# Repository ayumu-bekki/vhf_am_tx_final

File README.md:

# VHF AM 送信用ファイナル段

VHF帯(144MHz)AM送信用ファイナル段の試験基板です。

## 仕様

| 項目 | 値 |
|------|-----|
| 電源電圧 | 5V〜7.2V |
| 対応MOSFET | 2SK3074 / HTL7G06S006P |

### 出力電力・入力レベル

| 電源 | MOSFET | 出力電力 | 入力レベル |
|------|--------|----------|------------|
| 5V | 2SK3074 | 125mW | 10mW (+10dBm / 2.0Vpp) |
| 7.2V | 2SK3074 | 500mW | 50mW (+17dBm / 4.5Vpp) |
| 5V | HTL7G06S006P | 750mW | 10mW (+10dBm / 2.0Vpp) |
| 7.2V | HTL7G06S006P | 1500mW | 20mW (+13dBm / 2.8Vpp) |

---

## インダクタの製作

### L2(フェライトコアチョークコイル)

- コア : 43材フェライトコア(例：FT-37-43)
- 線材 : 0.65mm ポリウレタン銅線
- 巻き数
  - 3.3μH : 3回巻き

### L1, L3, L4, L5(空芯コイル)

- 線材 : 0.8mm ポリウレタン銅線
- コア : 空芯(外径5mmの軸を型に使用)
- 巻き数
  - 50nH : 3回巻き
  - 80nH : 4回巻き

---

## MOSFETごとの実装変更

### 2SK3074 の場合

- 回路図通りに実装する

### HTL7G06S006P の場合

- 以下のパーツを変更する

| 部位 | 部品 | 変更内容 |
|------|------|----------|
| 入力マッチング | C3 | 50pF トリマ |
| 出力マッチング | L3 | 40nH(2〜3回巻き) |
| 出力マッチング | C8 | 47pF を実装する |

---

## 調整方法

### 必要な機器

- 電流計
- NanoVNA
- TinySA

---

### 1. バイアス調整(アイドリング電流の設定)

FETがAB級リニアアンプとして動作するよう、無信号時のアイドリング電流を設定します。

**準備**

1. RF信号は入力しない
2. RV1を絞る(ゲート電圧が最低になる方向)
3. 電源ラインに電流計を直列に接続

**手順**

1. 電源を入れる(この時点では数mA程度しか流れない)
2. RV1をゆっくり回していくと、電流が流れ始める点がある
3. 電流が **20〜30mA** になる位置でRV1を止める

---

### 2. 入力マッチング調整

NanoVNAを使って、アンプ入力のインピーダンスを50Ωに合わせます。
電源は入れた状態で測定する必要があります。

1. NanoVNAを144MHz中心にスキャン設定し、S11(反射係数 / SWR)を表示
2. NanoVNA CH0をアンプの入力コネクタ(J1)に接続
3. スミスチャートまたはSWRグラフを見ながら、トリマコンデンサ **C1** を回して **144MHzでSWR最小** となる点に合わせる

---

### 3. 出力マッチング調整

実際に電源・RF信号を入力して出力パワーを最大化します。

1. 入力(J1)に144MHzの信号源を接続
2. 出力(J3)に30dBアッテネータ → TinySA を接続
3. TinySAで144MHz付近のスペクトラムを表示
4. アンテナ側トリマ **C6** を回してピークが最大になる点を探す
5. FET側トリマ **C4** を回してさらにピークが高くなる点を探す
6. C6とC4を交互に調整し、ピーク点を追い込む

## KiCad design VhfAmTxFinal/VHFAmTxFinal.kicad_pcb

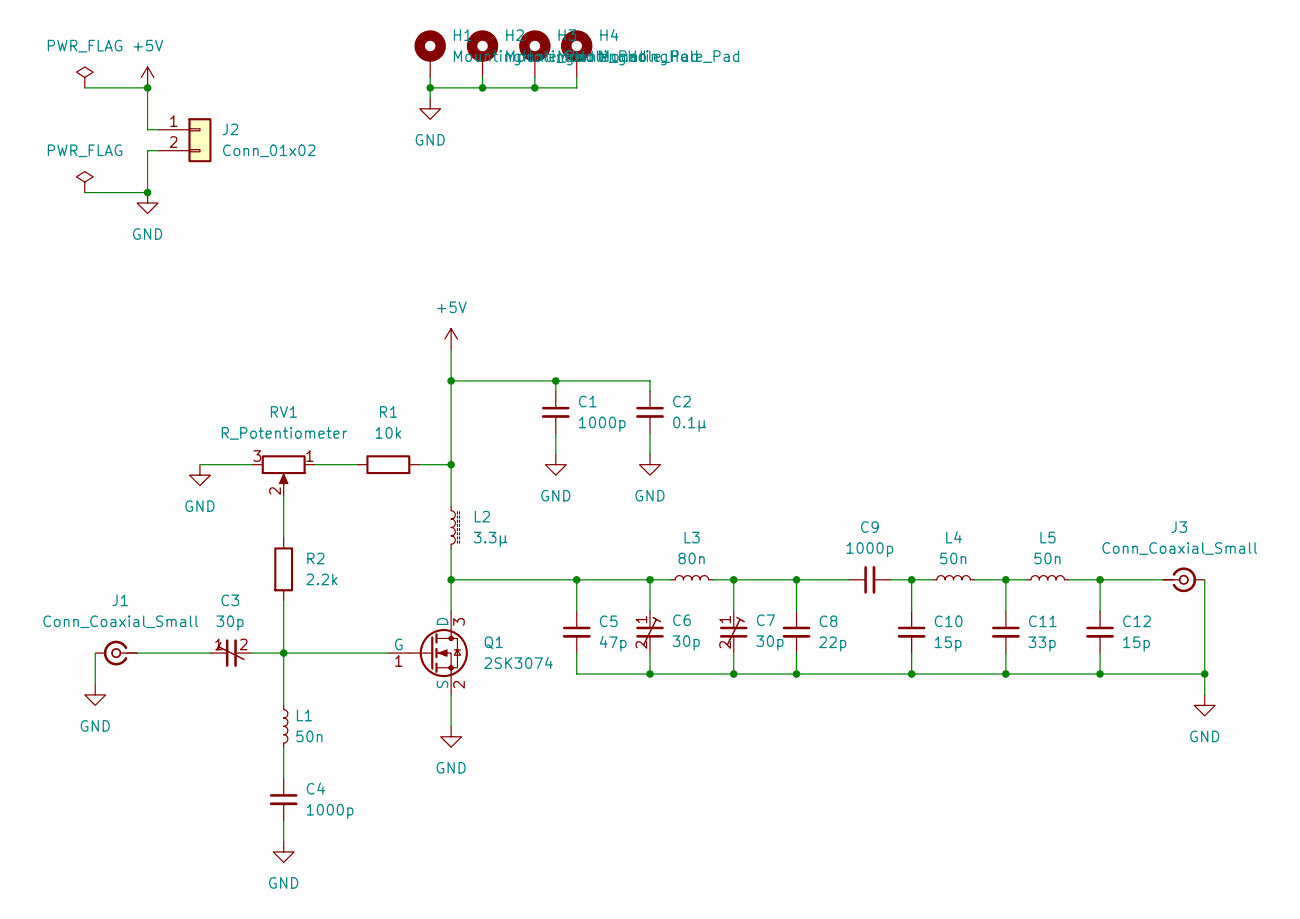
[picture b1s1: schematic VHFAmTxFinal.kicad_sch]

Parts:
C1, C4, C9: 1000p; C_0603_1608Metric_Pad1.08x0.95mm_HandSolder
C2: 0.1μ; C_0603_1608Metric_Pad1.08x0.95mm_HandSolder
C3, C6, C7: 30p; Ceramic_Trimmer_Capacitors_THT
C5: 47p; C_0603_1608Metric_Pad1.08x0.95mm_HandSolder
C8: 22p; C_0603_1608Metric_Pad1.08x0.95mm_HandSolder
C10, C12: 15p; C_0603_1608Metric_Pad1.08x0.95mm_HandSolder
C11: 33p; C_0603_1608Metric_Pad1.08x0.95mm_HandSolder
H1, H2, H3, H4: MountingHole_Pad; MountingHole_3.2mm_M3_Pad_Via
J1, J3: Conn_Coaxial_Small; SMA_S-063-49-TGG_EdgeMount_Horizontal
J2: Conn_01x02; JST_XH_S2B-XH-A_1x02_P2.50mm_Horizontal
L1, L4, L5: 50n; Air_Core_Inductor_8mm
L2: 3.3μ; Choke_Inductor_10mm
L3: 80n; Air_Core_Inductor_8mm
Q1: 2SK3074; SOT-89-3_Handsoldering
R1: 10k; R_0603_1608Metric_Pad0.98x0.95mm_HandSolder
R2: 2.2k; R_0603_1608Metric_Pad0.98x0.95mm_HandSolder
RV1: R_Potentiometer; Potentiometer_Vishay_T73YP_Vertical

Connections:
+5V: C1.1, C2.1, J2.1, L2.1, R1.2
GND: C1.2, C2.2, C4.2, C5.2, C6.2, C7.2, C8.2, C10.2, C11.2, C12.2, H1.1, H2.1, H3.1, H4.1, J1.2 (Ext), J2.2, J3.2 (Ext), Q1.2 (S), RV1.3
unnamed: C4.1, L1.2
unnamed: C7.1, C8.1, C9.1, L3.2
unnamed: C9.2, C10.1, L4.1
unnamed: C11.1, L4.2, L5.1
unnamed: C3.1, J1.1 (In)
unnamed: C12.1, J3.1 (In), L5.2
unnamed: C5.1, C6.1, L2.2, L3.1, Q1.3 (D)
unnamed: C3.2, L1.1, Q1.1 (G), R2.2
unnamed: R1.1, RV1.1
unnamed: R2.1, RV1.2

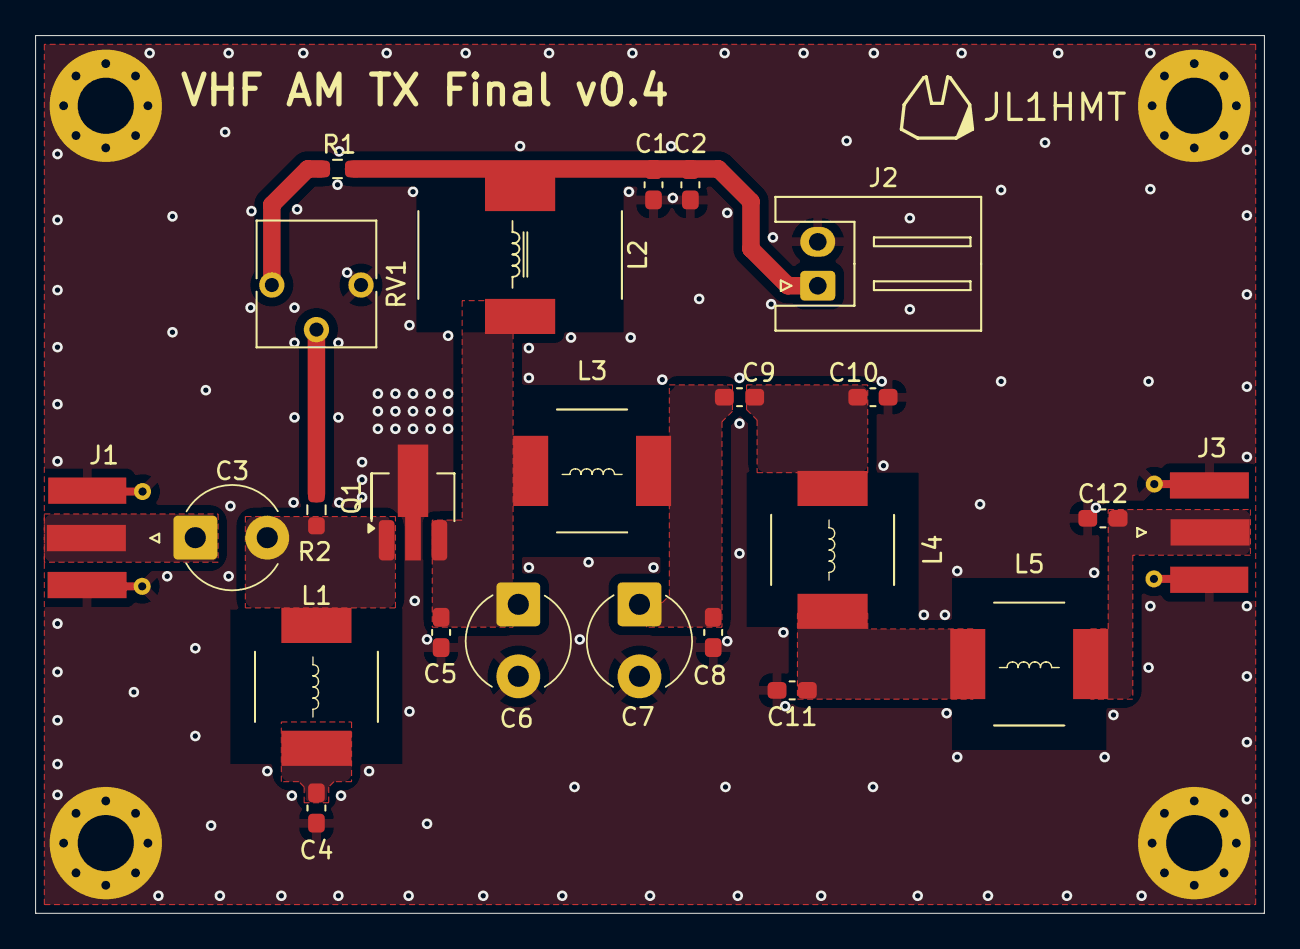
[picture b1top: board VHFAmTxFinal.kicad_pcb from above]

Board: 2 copper layers, 70.0 x 50.0 mm, 28 parts (0 on the bottom side), 12 nets.

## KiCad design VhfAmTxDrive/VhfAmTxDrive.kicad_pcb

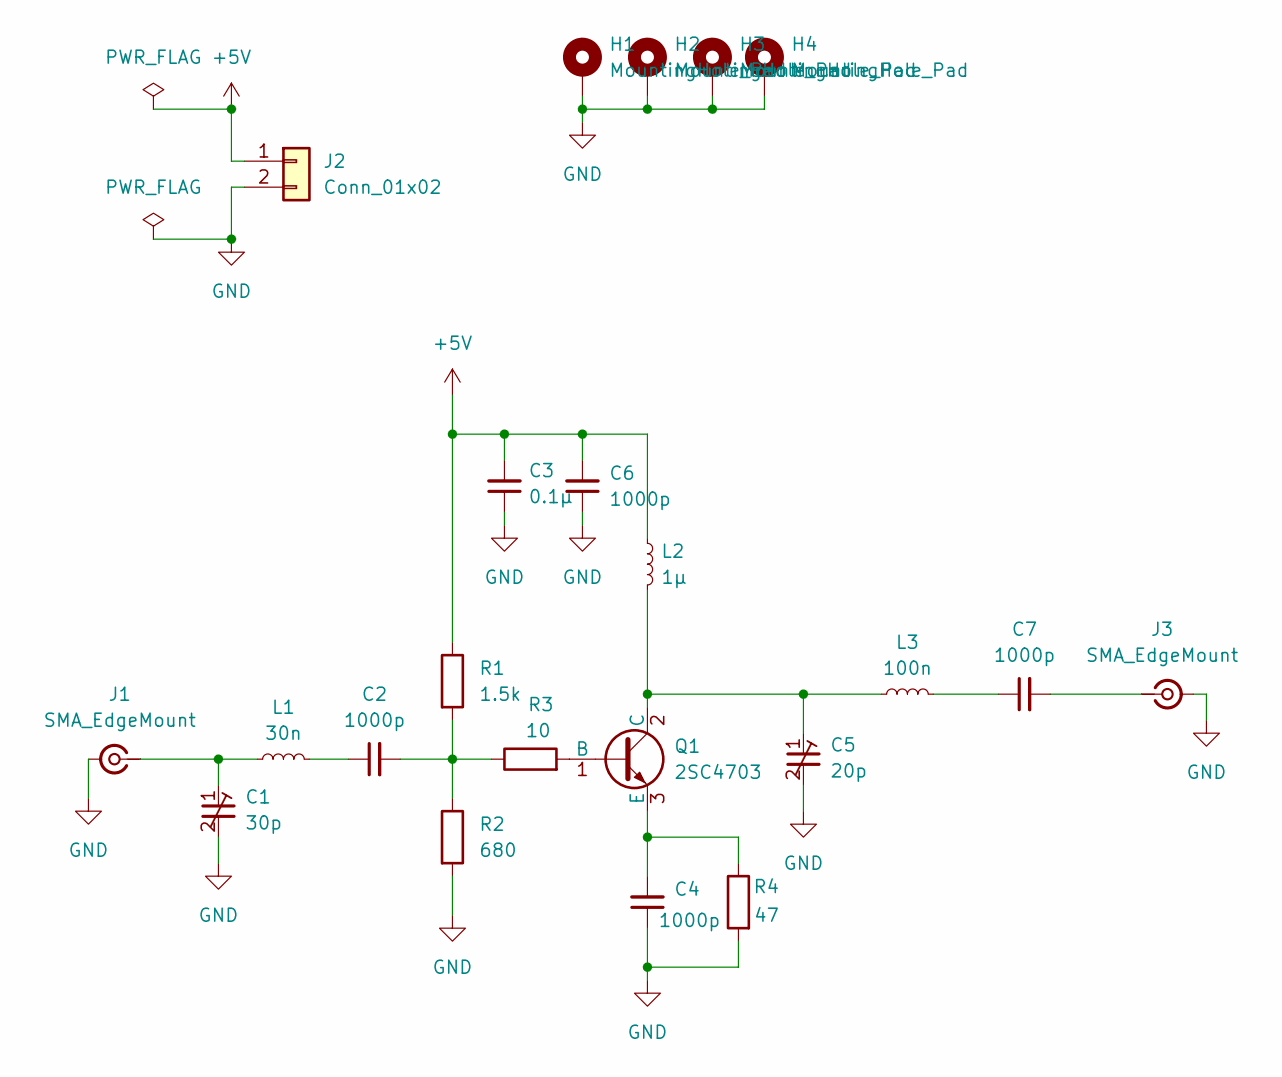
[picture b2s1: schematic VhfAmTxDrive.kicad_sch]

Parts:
C1: 30p; Ceramic_Trimmer_Capacitors_THT
C2, C4, C6, C7: 1000p; C_0603_1608Metric_Pad1.08x0.95mm_HandSolder
C3: 0.1μ; C_0603_1608Metric_Pad1.08x0.95mm_HandSolder
C5: 20p; Ceramic_Trimmer_Capacitors_THT
H1, H2, H3, H4: MountingHole_Pad; MountingHole_3.2mm_M3_Pad_Via
J1, J3: SMA_EdgeMount; SMA_S-063-49-TGG_EdgeMount_Horizontal
J2: Conn_01x02; JST_XH_S2B-XH-A_1x02_P2.50mm_Horizontal
L1: 30n; Air_Core_Inductor_8mm
L2: 1μ; Air_Core_Inductor_8mm
L3: 100n; Air_Core_Inductor_12mm
Q1: 2SC4703
R1: 1.5k; R_0603_1608Metric_Pad0.98x0.95mm_HandSolder
R2: 680; R_0603_1608Metric_Pad0.98x0.95mm_HandSolder
R3: 10; R_0603_1608Metric_Pad0.98x0.95mm_HandSolder
R4: 47; R_0603_1608Metric_Pad0.98x0.95mm_HandSolder

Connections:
+5V: C3.2, C6.2, J2.1, L2.1, R1.1
GND: C1.2, C3.1, C4.1, C5.2, C6.1, H1.1, H2.1, H3.1, H4.1, J1.2 (Ext), J2.2, J3.2 (Ext), R2.2, R4.2
unnamed: C2.1, L1.2
unnamed: C2.2, R1.2, R2.1, R3.1
unnamed: C7.1, L3.2
unnamed: C1.1, J1.1 (In), L1.1
unnamed: C7.2, J3.1 (In)
unnamed: Q1.1 (B), R3.2
unnamed: C5.1, L2.2, L3.1, Q1.2 (C)
unnamed: C4.2, Q1.3 (E), R4.1

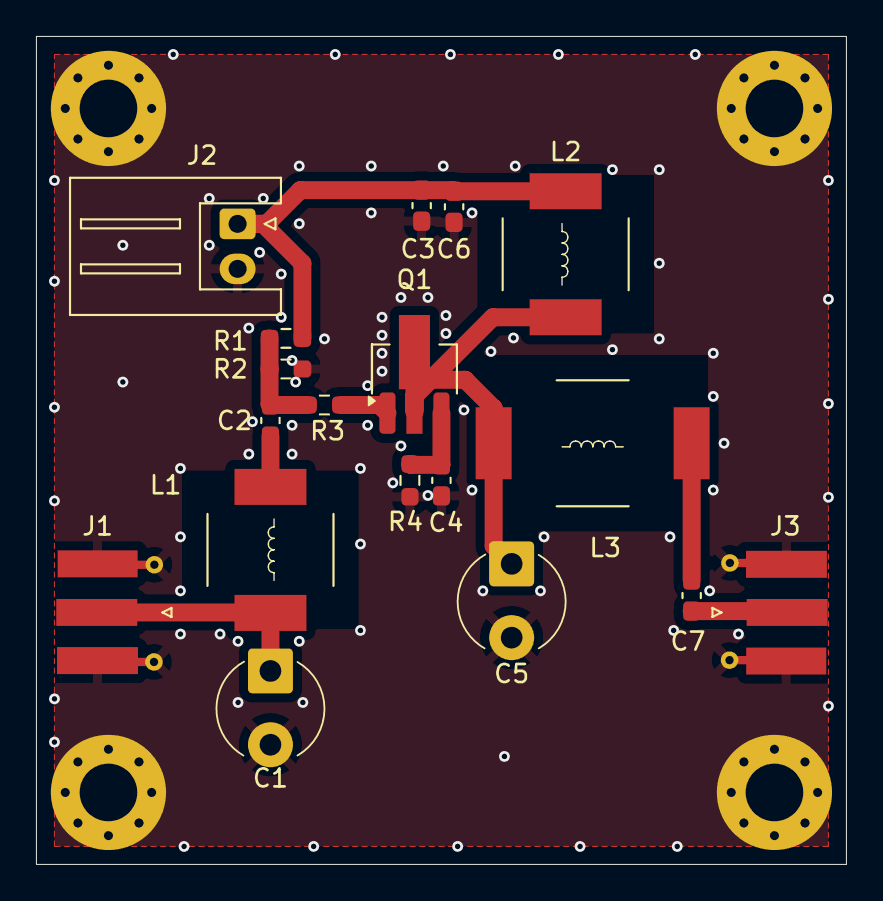
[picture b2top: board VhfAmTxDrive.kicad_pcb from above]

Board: 2 copper layers, 45.0 x 46.0 mm, 22 parts (0 on the bottom side), 10 nets.

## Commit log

2026-03-11 add pcb
2026-03-11 バイアス電圧用調整・安全用抵抗の追加とレイアウト修正
2026-03-11 HTL7G06S006Pの対応 READMEアップデート
2026-03-13 基板のレイアウト修正 v0.3
2026-03-21 ドキュメント修正ドライブ段を追加
2026-03-30 基板修正
